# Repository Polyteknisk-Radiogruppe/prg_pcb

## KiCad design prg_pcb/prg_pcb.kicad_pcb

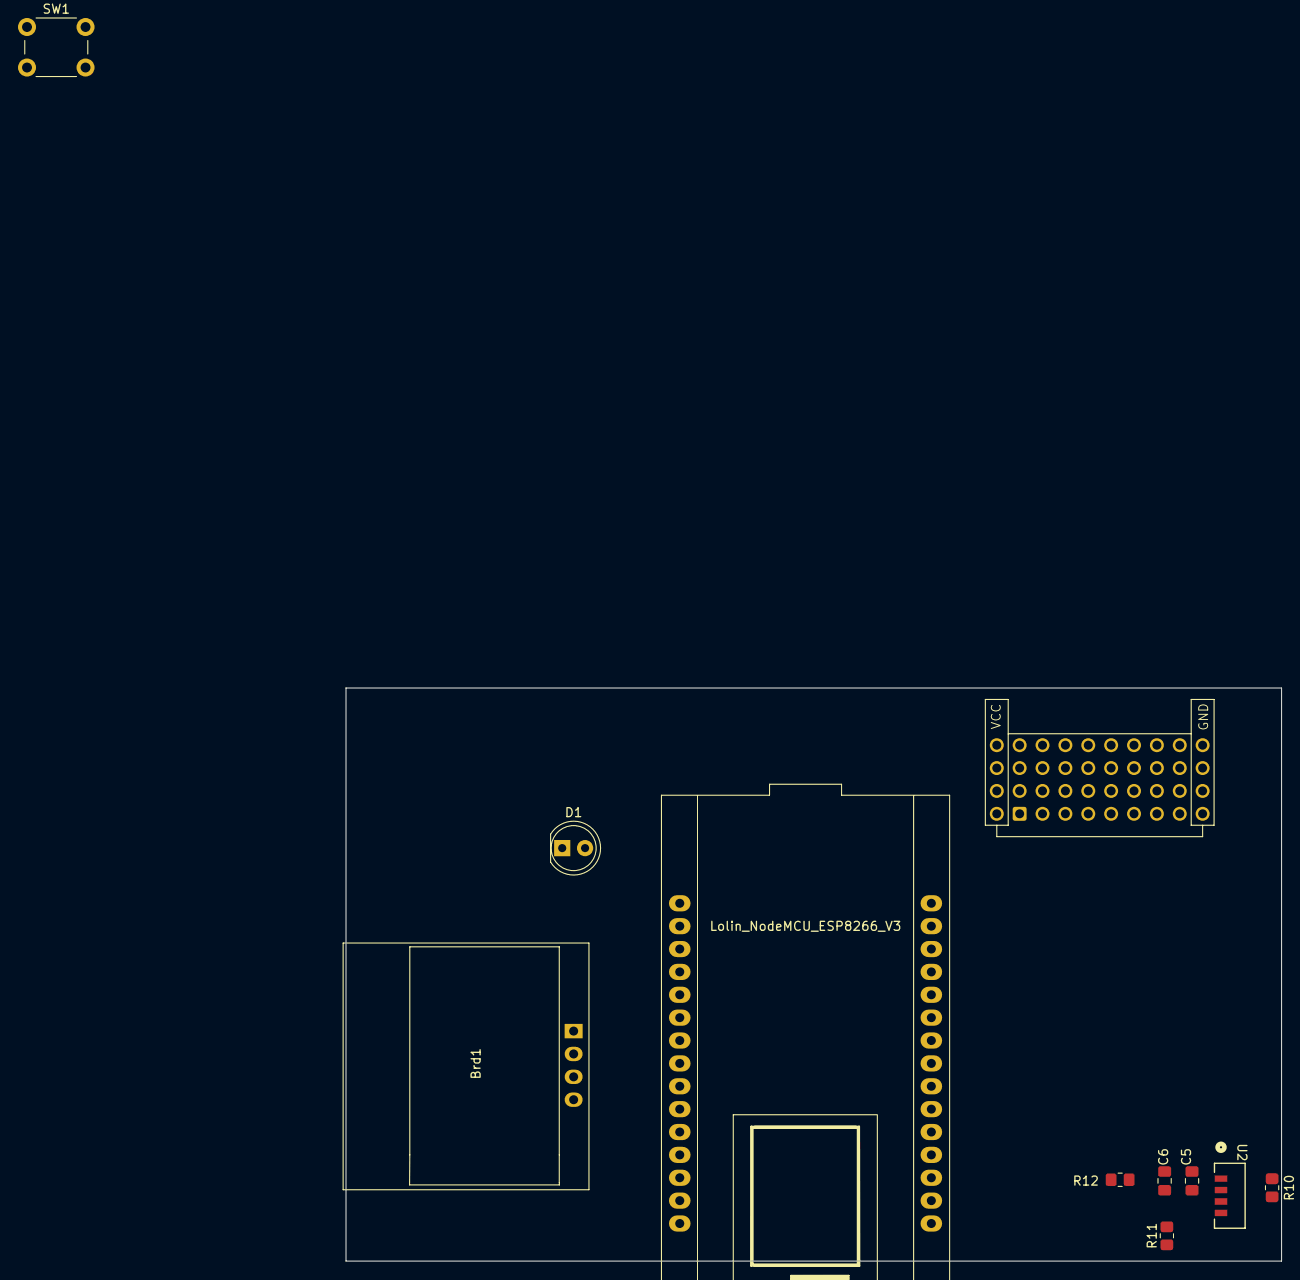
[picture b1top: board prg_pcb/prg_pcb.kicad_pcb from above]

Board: 2 copper layers, 103.9 x 63.6 mm, 11 parts (0 on the bottom side), 6 nets, no tracks yet.

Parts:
A2: Lolin_NodeMCU_ESP8266_V3; Lolin_NodeMCU_ESP8266
Brd1: SSD1306; ssd1306
C5: 10u; C_0805_2012Metric_Pad1.18x1.45mm_HandSolder
C6: 100n; C_0805_2012Metric_Pad1.18x1.45mm_HandSolder
D1: LED; LED_D5.0mm
J1: 3x10_connector_THT
R10, R11: 4k; R_0805_2012Metric_Pad1.20x1.40mm_HandSolder
R12: 10; R_0805_2012Metric_Pad1.20x1.40mm_HandSolder
SW1: Button; SW_PUSH_6mm
U2: VEML7700-TR

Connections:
GND: A2.2 (GND), A2.9 (GND), A2.17 (GND), A2.25 (GND), A2.29 (GND), Brd1.1 (GND), C5.2, C6.2, J1.a1 (GND), U2.3 (GND)
LED: A2.12 (D3/GPIO0), D1.2
unnamed: C5.1, C6.1, R12.1, U2.2 (VDD)
SCL: A2.14 (D1/GPIO5/SCL), Brd1.3 (SCL), R10.2, U2.1 (SCL)
SDA: A2.13 (D2/GPIO4/SDA), Brd1.4 (SDA), R11.2, U2.4 (SDA)
VCC: A2.1 (3V3), A2.10 (3V3), A2.26 (3V3), Brd1.2 (VCC), J1.c1 (VCC), R10.1, R11.1, R12.2, SW1.2

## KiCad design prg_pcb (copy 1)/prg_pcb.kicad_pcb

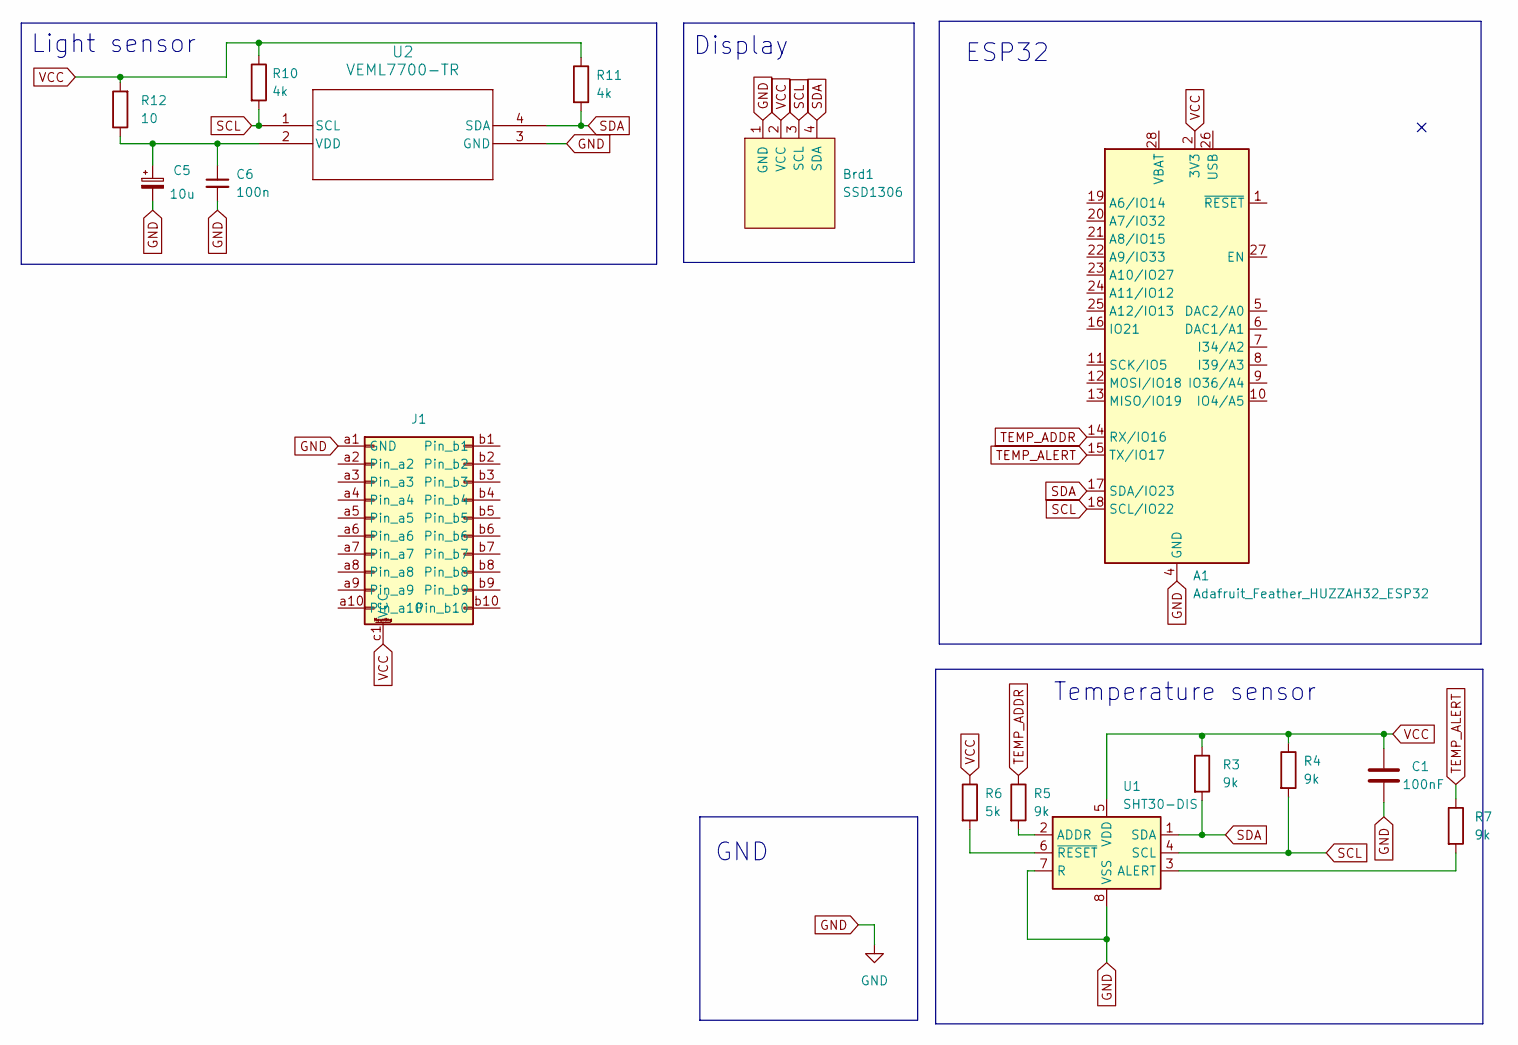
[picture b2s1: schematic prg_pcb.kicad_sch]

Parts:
A1: Adafruit_Feather_HUZZAH32_ESP32; Adafruit_Feather
Brd1: SSD1306; ssd1306
C1: 100nF; C_0805_2012Metric_Pad1.18x1.45mm_HandSolder
C5: 10u; C_0805_2012Metric_Pad1.18x1.45mm_HandSolder
C6: 100n; C_0805_2012Metric_Pad1.18x1.45mm_HandSolder
J1: 3x10_connector_THT
R3, R4, R5, R7: 9k; R_0805_2012Metric_Pad1.20x1.40mm_HandSolder
R6: 5k; R_0805_2012Metric_Pad1.20x1.40mm_HandSolder
R10, R11: 4k; R_0805_2012Metric_Pad1.20x1.40mm_HandSolder
R12: 10; R_0805_2012Metric_Pad1.20x1.40mm_HandSolder
U1: SHT30-DIS; Sensirion_DFN-8-1EP_2.5x2.5mm_P0.5mm_EP1.1x1.7mm
U2: VEML7700-TR

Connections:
GND: A1.4 (GND), Brd1.1 (GND), C1.2, C5.2, C6.2, J1.a1 (GND), U1.7 (R), U1.8 (VSS), U1.9 (VSS), U2.3 (GND)
unnamed: R5.2, U1.2 (ADDR)
unnamed: R7.2, U1.3 (ALERT)
unnamed: R6.2, U1.6 (~RESET)
unnamed: C5.1, C6.1, R12.1, U2.2 (VDD)
SCL: A1.18 (SCL/IO22), Brd1.3 (SCL), R4.2, R10.2, U1.4 (SCL), U2.1 (SCL)
SDA: A1.17 (SDA/IO23), Brd1.4 (SDA), R3.2, R11.2, U1.1 (SDA), U2.4 (SDA)
TEMP_ADDR: A1.14 (RX/IO16), R5.1
TEMP_ALERT: A1.15 (TX/IO17), R7.1
VCC: A1.2 (3V3), Brd1.2 (VCC), C1.1, J1.c1 (VCC), R3.1, R4.1, R6.1, R10.1, R11.1, R12.2, U1.5 (VDD)

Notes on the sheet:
Temperature sensor
Display
Light sensor
ESP32
GND

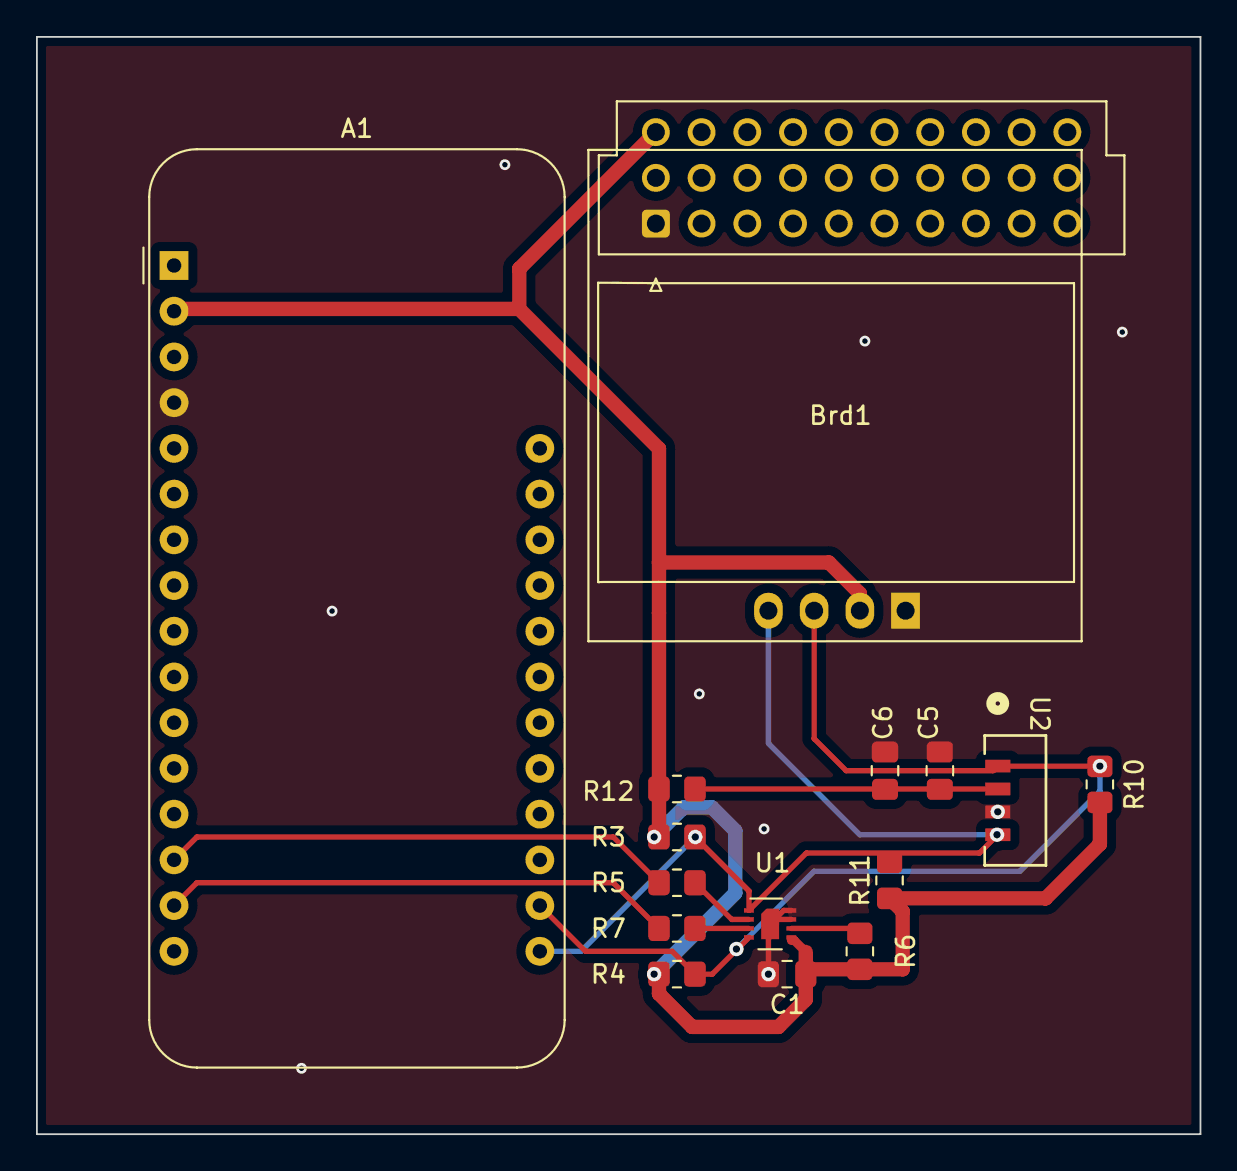
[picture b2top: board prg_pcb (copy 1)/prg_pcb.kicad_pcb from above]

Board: 2 copper layers, 64.6 x 61.0 mm, 16 parts (0 on the bottom side), 10 nets.

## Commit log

2024-03-25 Upload
2024-03-26 kicad dru
2024-09-15 Cleanup
2024-09-15 cleanup whoops
2024-09-15 fixing VEML7700
2024-09-15 Getting ready
